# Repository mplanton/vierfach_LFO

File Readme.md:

# Vierfach LFO Eurorack Module

This is a quadruple LFO eurorack module.
The original LFO schematic is found in Barry Klein's [Electronic music circuits](https://archive.org/details/electronic-music-circuits/page/n71/mode/2up) on page 70.

Every LFO features a switchable output for pulse, triangle or sine.

See the [pictures](pic/) for the assembly process.
The module is a rough prototype I built for my own purposes and I hope you may find it useful for your own projects.

Manuel Planton 2022

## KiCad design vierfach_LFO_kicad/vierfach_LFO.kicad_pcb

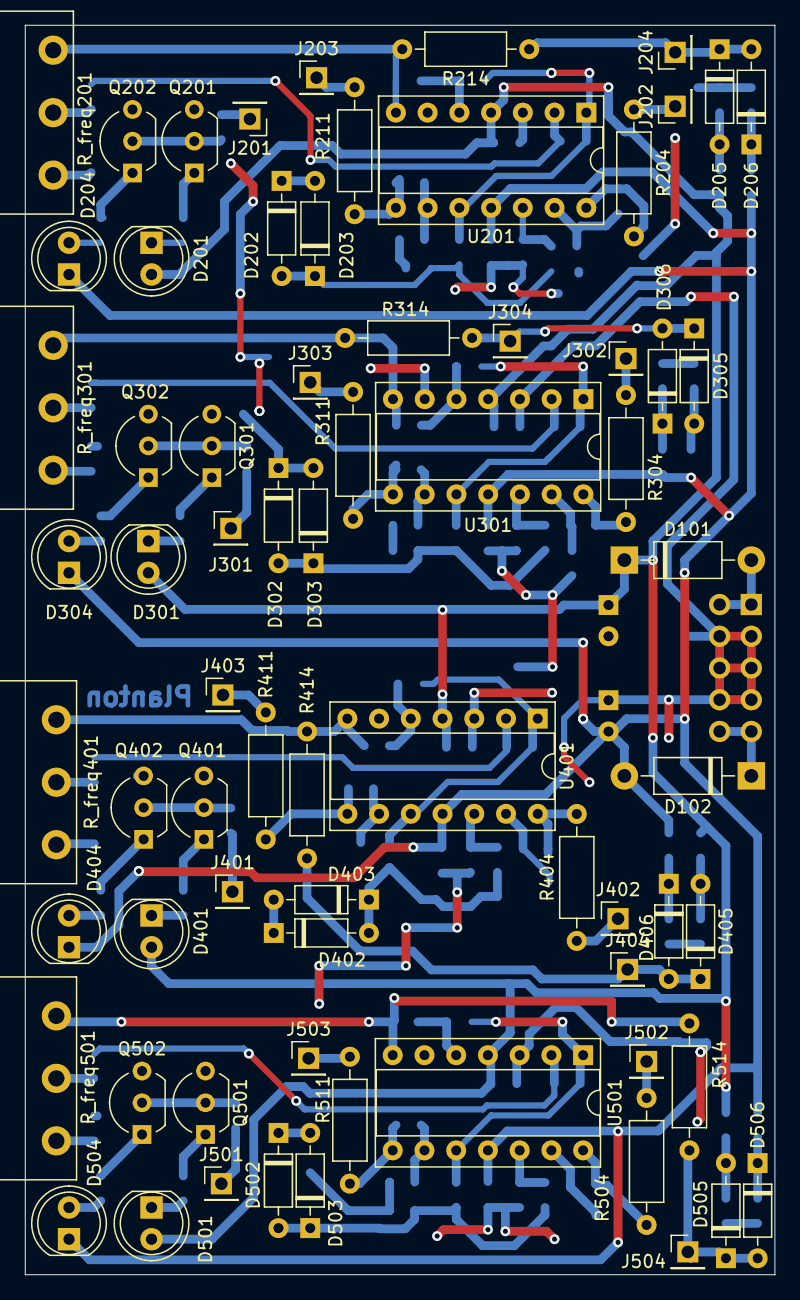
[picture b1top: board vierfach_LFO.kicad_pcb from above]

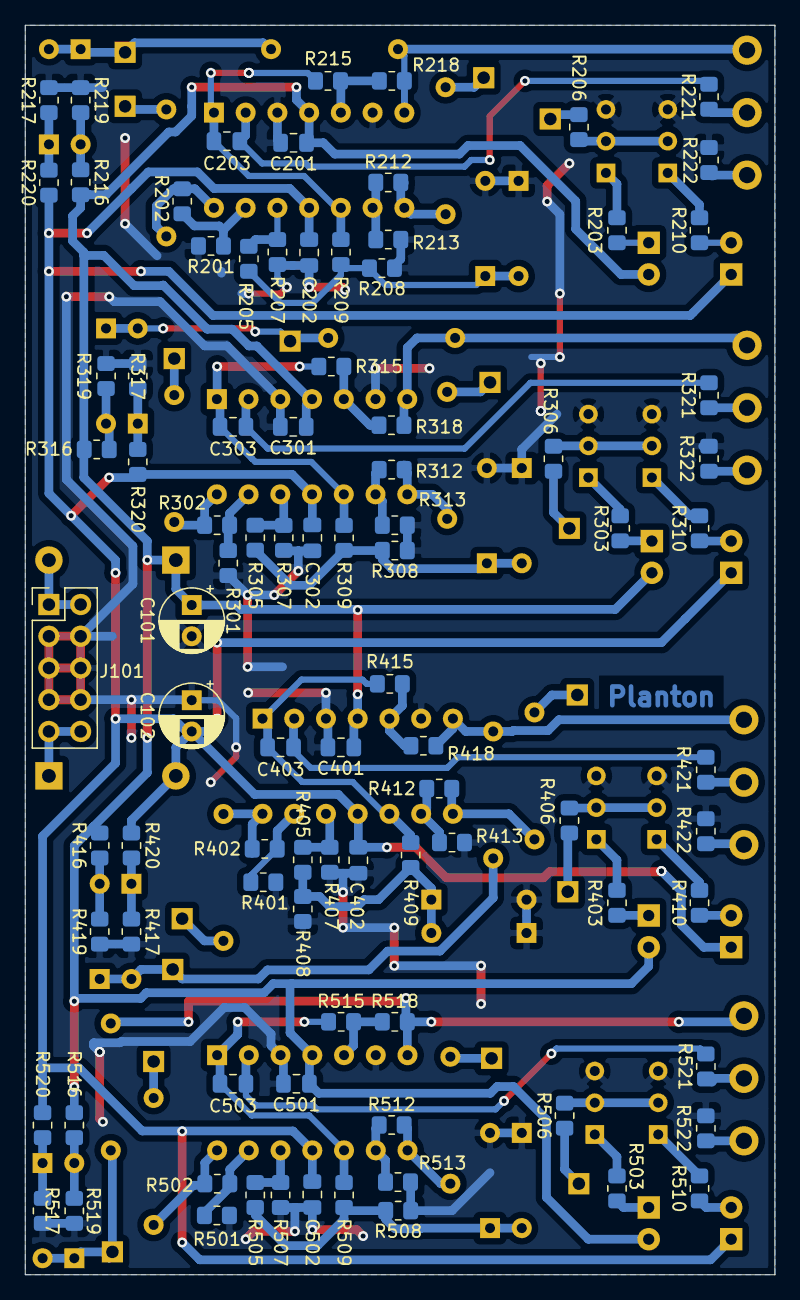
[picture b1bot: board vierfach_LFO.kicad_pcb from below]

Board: 2 copper layers, 60.0 x 100.0 mm, 161 parts (91 on the bottom side), 97 nets.

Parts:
C101, C102: 10u; CP_Radial_D5.0mm_P2.50mm
C201, C202, C203, C301, C302, C303, C401, C402, C403, C501, C502, C503: 100n; C_0805_2012Metric_Pad1.18x1.45mm_HandSolder
D101, D102: 1N5817; D_DO-41_SOD81_P10.16mm_Horizontal
D201, D301, D401, D501: green; LED_D5.0mm
D202, D203, D205, D206, D302, D303, D305, D306, D402, D403, D405, D406, D502, D503, D505, D506: 1N4148; D_DO-35_SOD27_P7.62mm_Horizontal
D204, D304, D404, D504: red; LED_D5.0mm
J101: Conn_02x05_Odd_Even; PinHeader_2x05_P2.54mm_Vertical
J201, J301, J401, J501: LEDs_IN_Conn_01x01_Female; PinHeader_1x01_P2.54mm_Vertical
J202, J302, J402, J502: sine_OUT_Conn_01x01_Female; PinHeader_1x01_P2.54mm_Vertical
J203, J303, J403, J503: tri_OUT_Conn_01x01_Female; PinHeader_1x01_P2.54mm_Vertical
J204, J304, J404, J504: square_OUT_Conn_01x01_Female; PinHeader_1x01_P2.54mm_Vertical
Q201, Q301, Q401, Q501: BC547; TO-92_Inline_Wide
Q202, Q302, Q402, Q502: BC557; TO-92_Inline_Wide
R201, R205, R208, R222, R301, R305, R308, R322, R401, R405, R408, R422, R501, R505, R508, R522: 1k; R_0805_2012Metric_Pad1.20x1.40mm_HandSolder
R202, R207, R212, R213, R215, R302, R307, R312, R313, R315, R402, R407, R412, R413, R415, R502, R507, R512, R513, R515: 10k; R_0805_2012Metric_Pad1.20x1.40mm_HandSolder
R203, R209, R210, R303, R309, R310, R403, R409, R410, R503, R509, R510: 2.2k; R_0805_2012Metric_Pad1.20x1.40mm_HandSolder
R204, R211, R214, R304, R311, R314, R404, R411, R414, R504, R511, R514: 1k; R_Axial_DIN0207_L6.3mm_D2.5mm_P10.16mm_Horizontal
R206, R306, R406, R506: 1M; R_0805_2012Metric_Pad1.20x1.40mm_HandSolder
R216, R217, R219, R220, R316, R317, R319, R320, R416, R417, R419, R420, R516, R517, R519, R520: 4.7k; R_0805_2012Metric_Pad1.20x1.40mm_HandSolder
R218, R318, R418, R518: 33k; R_0805_2012Metric_Pad1.20x1.40mm_HandSolder
R221, R321, R421, R521: 470k; R_0805_2012Metric_Pad1.20x1.40mm_HandSolder
R_freq201, R_freq301, R_freq401, R_freq501: 1M; Potentiometer_Piher_PC-16_Single_Horizontal
U201, U301, U401, U501: TL074; DIP-14_W7.62mm_Socket

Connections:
+12V: D101.2, J101.1, J101.2
-12V: D102.1, J101.9, J101.10
/LFO_voice_200/sine: J202.1, R204.1
/LFO_voice_200/square: D205.1, D206.2, J204.1, R214.1
/LFO_voice_200/triangle: J203.1, R211.1
/LFO_voice_300/sine: J302.1, R304.1
/LFO_voice_300/square: D305.1, D306.2, J304.1, R314.1
/LFO_voice_300/triangle: J303.1, R311.1
/LFO_voice_400/sine: J402.1, R404.1
/LFO_voice_400/square: D405.1, D406.2, J404.1, R414.1
/LFO_voice_400/triangle: J403.1, R411.1
/LFO_voice_500/sine: J502.1, R504.1
/LFO_voice_500/square: D505.1, D506.2, J504.1, R514.1
/LFO_voice_500/triangle: J503.1, R511.1
GND: C101.2, C102.1, C201.2, C202.1, C301.2, C302.1, C401.2, C402.1, C501.2, C502.1, D202.1, D203.2, D302.1, D303.2, D402.1, D403.2, D502.1, D503.2, J101.3, J101.4, J101.5, J101.6, J101.7, J101.8, Q201.3, Q202.3, Q301.3, Q302.3, Q401.3, Q402.3, Q501.3, Q502.3, R201.2, R207.1, R208.1, R213.1, R217.2, R219.1, R222.1, R301.2, R307.1, R308.1, R313.1, R317.2, R319.1, R322.1, R401.2, R407.1, R408.1, R413.1, R417.2, R419.1, R422.1, R501.2, R507.1, R508.1, R513.1, R517.2, R519.1, R522.1, U201.3, U201.6, U301.3, U301.6, U401.3, U401.6, U501.3, U501.6
unnamed: C203.1, R209.1, R215.2, U201.1, U201.10
unnamed: C203.2, R221.2, U201.2
unnamed: C303.1, R309.1, R315.2, U301.1, U301.10
unnamed: C303.2, R321.2, U301.2
unnamed: C403.1, R409.1, R415.2, U401.1, U401.10
unnamed: C403.2, R421.2, U401.2
unnamed: C503.1, R509.1, R515.2, U501.1, U501.10
unnamed: C503.2, R521.2, U501.2
unnamed: D201.1, R203.2
unnamed: D202.2, D203.1, R205.2, R208.2, R209.2
unnamed: D204.2, R210.1
unnamed: D205.2, R216.1, R219.2
unnamed: D206.1, R217.1, R220.2
unnamed: D301.1, R303.2
unnamed: D302.2, D303.1, R305.2, R308.2, R309.2
unnamed: D304.2, R310.1
unnamed: D305.2, R316.1, R319.2
unnamed: D306.1, R317.1, R320.2
unnamed: D401.1, R403.2
unnamed: D402.2, D403.1, R405.2, R408.2, R409.2
unnamed: D404.2, R410.1
unnamed: D405.2, R416.1, R419.2
unnamed: D406.1, R417.1, R420.2
unnamed: D501.1, R503.2
unnamed: D502.2, D503.1, R505.2, R508.2, R509.2
unnamed: D504.2, R510.1
unnamed: D505.2, R516.1, R519.2
unnamed: D506.1, R517.1, R520.2
unnamed: J201.1, R206.2
unnamed: J301.1, R306.2
unnamed: J401.1, R406.2
unnamed: J501.1, R506.2
unnamed: Q201.1, R203.1
unnamed: Q201.2, Q202.2, R206.1
unnamed: Q202.1, R210.2
unnamed: Q301.1, R303.1
unnamed: Q301.2, Q302.2, R306.1
unnamed: Q302.1, R310.2
unnamed: Q401.1, R403.1
unnamed: Q401.2, Q402.2, R406.1
unnamed: Q402.1, R410.2
unnamed: Q501.1, R503.1
unnamed: Q501.2, Q502.2, R506.1
unnamed: Q502.1, R510.2
unnamed: R201.1, R202.1, U201.13
unnamed: R202.2, R204.2, U201.14
unnamed: R205.1, R207.2, U201.12
unnamed: R211.2, R212.2, U201.8
unnamed: R212.1, R213.2, U201.9
unnamed: R214.2, R218.1, R_freq201.1, U201.7
unnamed: R215.1, R218.2, U201.5
unnamed: R221.1, R_freq201.2
unnamed: R222.2, R_freq201.3
unnamed: R301.1, R302.1, U301.13
unnamed: R302.2, R304.2, U301.14
unnamed: R305.1, R307.2, U301.12
unnamed: R311.2, R312.2, U301.8
unnamed: R312.1, R313.2, U301.9
unnamed: R314.2, R318.1, R_freq301.1, U301.7
unnamed: R315.1, R318.2, U301.5
unnamed: R321.1, R_freq301.2
unnamed: R322.2, R_freq301.3
unnamed: R401.1, R402.1, U401.13
unnamed: R402.2, R404.2, U401.14
unnamed: R405.1, R407.2, U401.12
unnamed: R411.2, R412.2, U401.8
unnamed: R412.1, R413.2, U401.9
unnamed: R414.2, R418.1, R_freq401.1, U401.7
unnamed: R415.1, R418.2, U401.5
unnamed: R421.1, R_freq401.2
unnamed: R422.2, R_freq401.3
unnamed: R501.1, R502.1, U501.13
unnamed: R502.2, R504.2, U501.14
unnamed: R505.1, R507.2, U501.12
unnamed: R511.2, R512.2, U501.8
unnamed: R512.1, R513.2, U501.9
unnamed: R514.2, R518.1, R_freq501.1, U501.7
unnamed: R515.1, R518.2, U501.5
unnamed: R521.1, R_freq501.2
unnamed: R522.2, R_freq501.3
VCC: C101.1, C201.1, C301.1, C401.1, C501.1, D101.1, D201.2, D301.2, D401.2, D501.2, R216.2, R316.2, R416.2, R516.2, U201.4, U301.4, U401.4, U501.4
VDD: C102.2, C202.2, C302.2, C402.2, C502.2, D102.2, D204.1, D304.1, D404.1, D504.1, R220.1, R320.1, R420.1, R520.1, U201.11, U301.11, U401.11, U501.11

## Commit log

2023-06-01 added docu
